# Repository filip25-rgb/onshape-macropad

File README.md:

# onshape-macropad
An Onshape macropad for the buttons i use most: sketch, extrude, line, corner rectangle, circle and dimension

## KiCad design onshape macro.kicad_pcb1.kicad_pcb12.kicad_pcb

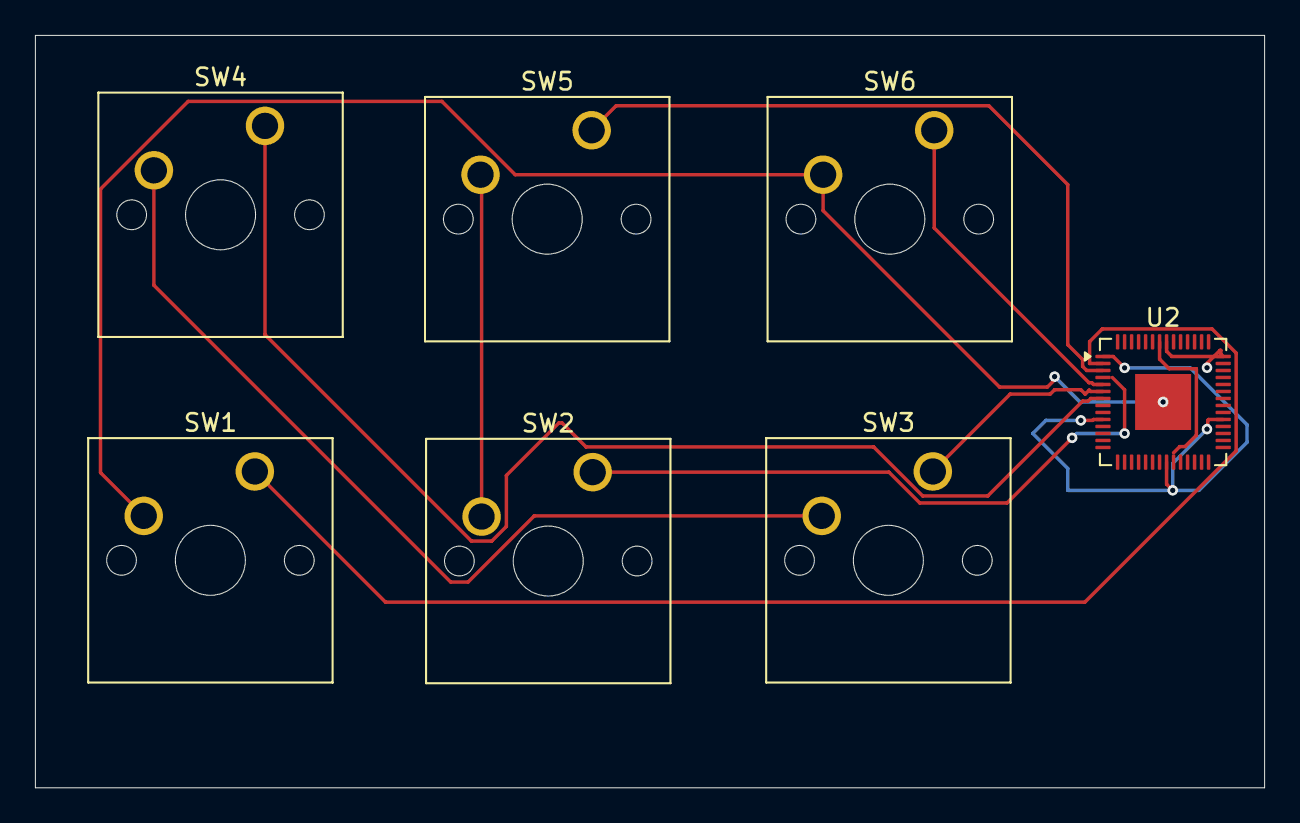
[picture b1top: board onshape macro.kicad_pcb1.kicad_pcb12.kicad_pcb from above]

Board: 2 copper layers, 70.2 x 43.0 mm, 7 parts (0 on the bottom side), 11 nets.

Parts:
SW1, SW2, SW3, SW4, SW5, SW6: SW_Push; SW_Cherry_MX_1.00u_PCB
U2: RP2040; QFN-56-1EP_7x7mm_P0.4mm_EP3.2x3.2mm

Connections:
GND: SW1.2, SW6.2, U2.57 (GND)
unnamed: SW2.2, SW5.2
unnamed: SW3.2, SW4.2
unnamed: U2.23 (DVDD), U2.50 (DVDD)
unnamed: SW1.1, U2.2 (GPIO0)
unnamed: SW5.1, U2.3 (GPIO1)
unnamed: SW2.1, U2.4 (GPIO2)
unnamed: SW6.1, U2.5 (GPIO3)
unnamed: SW3.1, U2.6 (GPIO4)
unnamed: SW4.1, U2.7 (GPIO5)
unnamed: U2.1 (IOVDD), U2.10 (IOVDD), U2.22 (IOVDD), U2.33 (IOVDD), U2.42 (IOVDD), U2.49 (IOVDD)

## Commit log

2026-06-27 kicad pcb design
